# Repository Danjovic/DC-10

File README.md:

# DC-10
My implementation of a clock using the C10 decimal time system

In the decimal time system one whole day is divided into 100 intervals which are subsequently divide into 100 'centivals' wich in turn are divided into 100 'ticks'.

Using more familiar base12 time base as a reference we have:

1 tick = 86,4ms

10 ticks = 864ms = 0,864 seconds (a bit less than a second)

100 ticks = 8,64 seconds = 1 centival

1000 ticks = 86,4 seconds = 10 centivals   (1 minute and 26 seconds)

10000 ticks = 864 seconds = 1 interval    (14 minutes and 24 seconds)

10000 ticks = 8640 seconds = 10 intervals (2 hours and 24 minutes)   

100000 ticks = 86400 seconds = 100 intervals (24 hours)

This project implements a very simple digital clock with 4 digits capable of showing centivals and intervals. The least significant digit changes each decival (8,64 seconds) and the most significant turns every 10 intervals (2 hours and 24 minutes)

The circuit is based on a PIC16F628 and four 7-segment displays in a conventional multiplex configuration. One of the displays is turned upside down so we can have two decimal points to separate intervals from decivals.  

The timebase is provided by a 4.0Mhz crystal which generates a tick (86,4ms) using a bresenham algorythm (code borrowed from Roman Black). As a result we have some microseconds of jitter yet imperceptible to the eye.

Each display is turned on by 4ms at a time which gives an overall display refresh rate of 16ms or ~60Hz in terms of frequency. 

There are two buttons to adjust the time. One is for advance the centivals while another advances the intervals. 

The circuit board measures 60x42mm (2.35" x 1.65") and it was designed to be single face friendly with few connections on the upper side and no connection on the top layer is hidden under any component.

The firmware uses the timer0 running at 1:1 thus overflowing exactly each 256us. At every 16 interrupts or 4096us a flag is set to allow the main loop to run. Another flag is set at each tick (86.4ms) and tells the main loop to increment the tick counter. At 100 ticks the main loop calls the function to increment the decivals and after 100 decivals another function is called to increment the intervals. Functions were used to implement the increments to make easy to perform the increments when commanded by the buttons.

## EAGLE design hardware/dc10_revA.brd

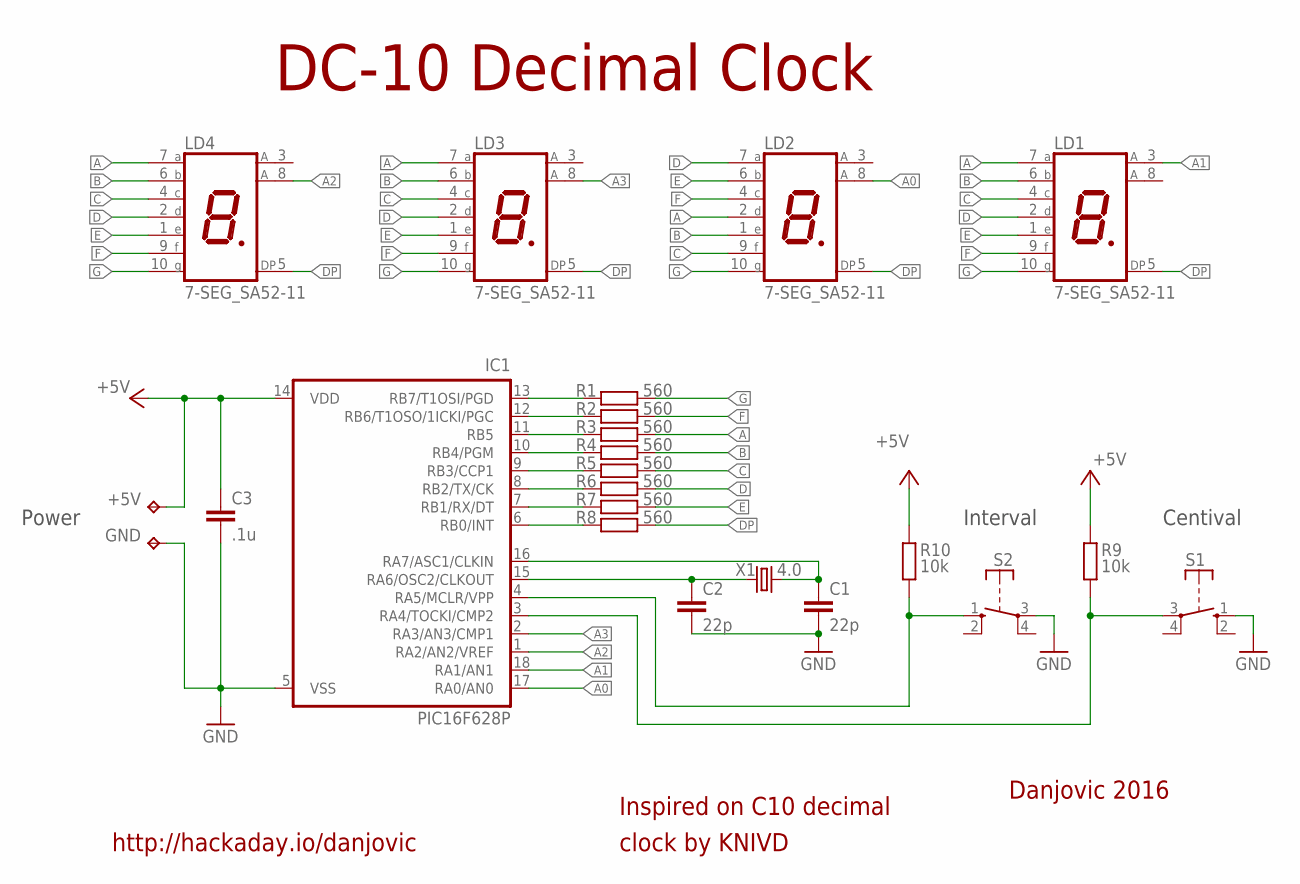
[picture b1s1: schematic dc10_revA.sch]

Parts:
+5V: TPPAD1-13; P1-13
C1, C2: 22p; C050-024X044
C3: .1u; C050-024X044
GND: TPPAD1-13; P1-13
IC1: PIC16F628P; DIL18
LD1, LD2, LD3, LD4: 7-SEG_SA52-11; SA52-11
R1, R2, R3, R4, R5, R6, R7, R8: 560; 0204/7
R9, R10: 10k; 0204/7
S1, S2: RACON12
X1: 4.0; HC49U-V

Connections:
+5V: +5V.1, C3.1, IC1.14 (VDD), R9.1, R10.1
A: LD1.7 (A), LD2.2 (D), LD3.7 (A), LD4.7 (A), R3.2
A0: IC1.17 (RA0/AN0), LD2.8 (A)
A1: IC1.18 (RA1/AN1), LD1.3 (A)
A2: IC1.1 (RA2/AN2/VREF), LD4.8 (A)
A3: IC1.2 (RA3/AN3/CMP1), LD3.8 (A)
A4: IC1.3 (RA4/TOCKI/CMP2), R9.2, S1.3
A5: IC1.4 (RA5/MCLR/VPP), R10.2, S2.1 (S)
B: LD1.6 (B), LD2.1 (E), LD3.6 (B), LD4.6 (B), R4.2
B0: IC1.6 (RB0/INT), R8.1
B1: IC1.7 (RB1/RX/DT), R7.1
B2: IC1.8 (RB2/TX/CK), R6.1
B3: IC1.9 (RB3/CCP1), R5.1
B4: IC1.10 (RB4/PGM), R4.1
B5: IC1.11 (RB5), R3.1
B6: IC1.12 (RB6/T1OSO/1ICKI/PGC), R2.1
B7: IC1.13 (RB7/T1OSI/PGD), R1.1
C: LD1.4 (C), LD2.9 (F), LD3.4 (C), LD4.4 (C), R5.2
D: LD1.2 (D), LD2.7 (A), LD3.2 (D), LD4.2 (D), R6.2
DP: LD1.5 (DP), LD2.5 (DP), LD3.5 (DP), LD4.5 (DP), R8.2
E: LD1.1 (E), LD2.6 (B), LD3.1 (E), LD4.1 (E), R7.2
F: LD1.9 (F), LD2.4 (C), LD3.9 (F), LD4.9 (F), R2.2
G: LD1.10 (G), LD2.10 (G), LD3.10 (G), LD4.10 (G), R1.2
GND: C1.2, C2.2, C3.2, GND.1, IC1.5 (VSS), S1.1 (S), S2.3
OSC1: C1.1, IC1.16 (RA7/ASC1/CLKIN), X1.2
OSC2: C2.1, IC1.15 (RA6/OSC2/CLKOUT), X1.1

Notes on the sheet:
Interval
Centival
Power
DC-10 Decimal Clock
http://hackaday.io/danjovic
Danjovic 2016
Inspired on C10 decimal
clock by KNIVD

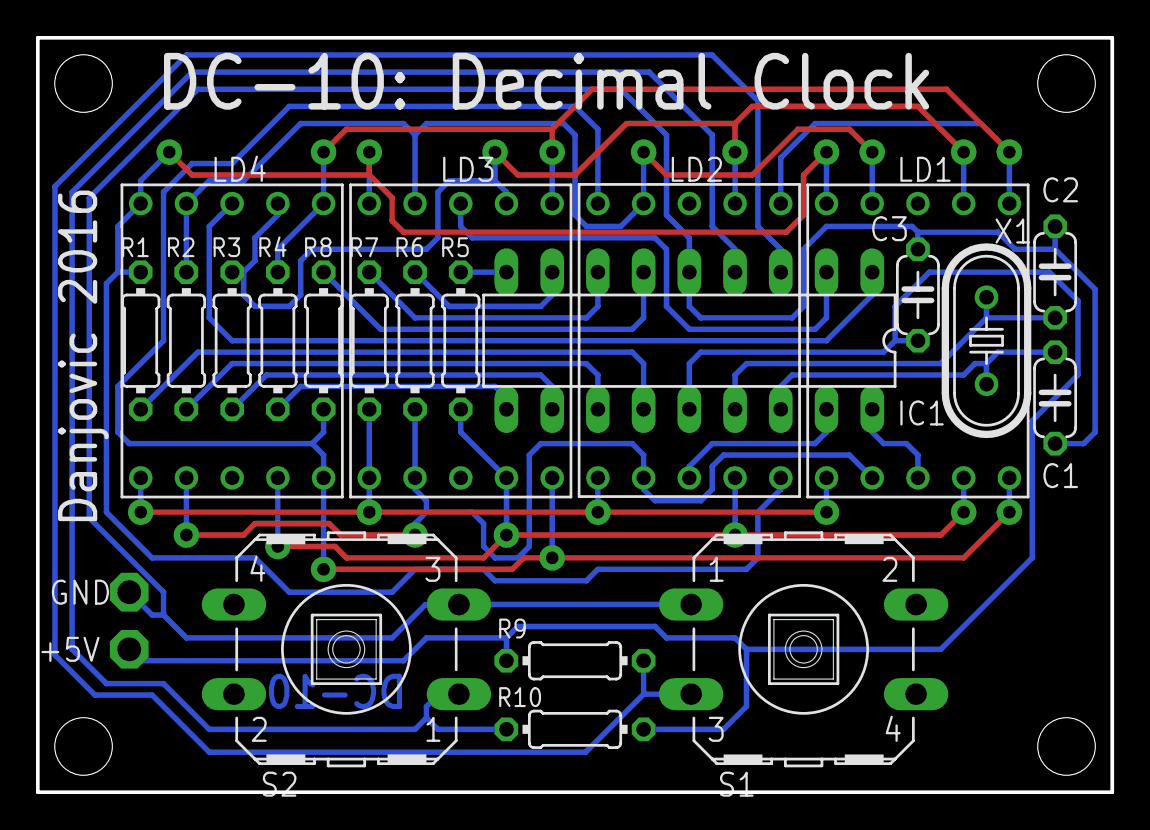
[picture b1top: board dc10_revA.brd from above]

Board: 2 copper layers, 59.7 x 41.9 mm, 23 parts (0 on the bottom side), 26 nets.

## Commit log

2016-04-24 Basic Release
2016-11-26 First run on prototype
2016-11-26 Button behavior corrected
2016-12-04 Revised PCB / Clock set tool
    Increased spacing between tracks to ease the production of homemade
    boards.
    Added a python script to generate dual clock with conventional and
    decimal time.
2016-12-04 corrected unintentional code merge
2016-12-04 Clock now has Hackaday colors
2016-12-04 Change Colors
2016-12-04 Corrected offset time
    Needed to delay 6 hours instead of advance 6 hours. Then 18 hours were added to localtime
2017-03-12 Update makefile
